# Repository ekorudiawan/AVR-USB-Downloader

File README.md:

# AVR-USB-Downloader
AVR USB Downloader

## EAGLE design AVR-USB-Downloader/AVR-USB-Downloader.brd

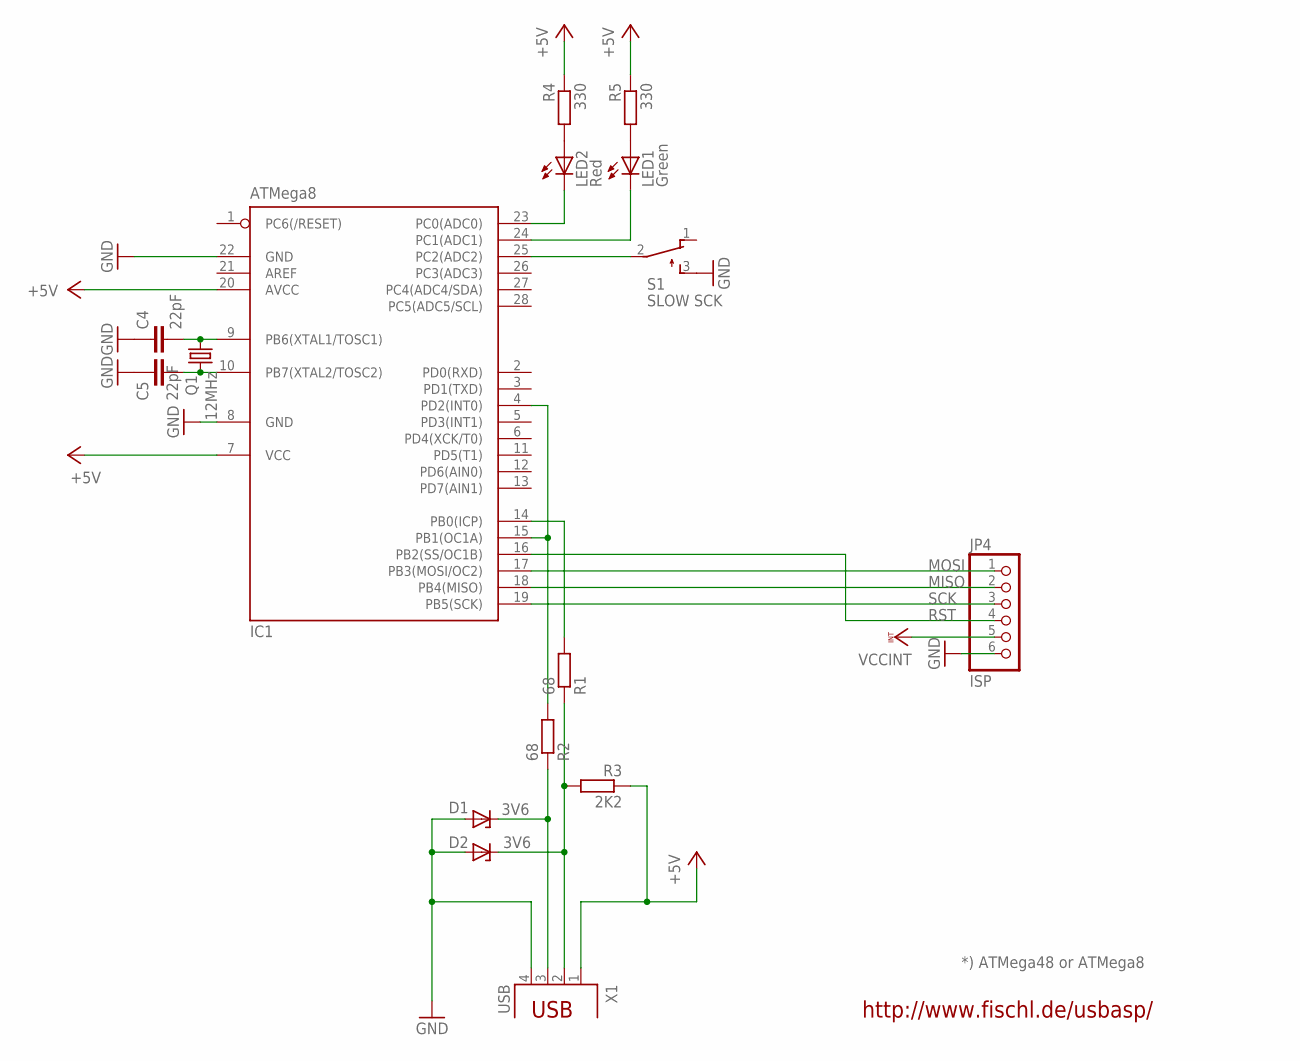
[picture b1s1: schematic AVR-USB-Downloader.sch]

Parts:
C4, C5: 22pF; C025-024X044
D1, D2: 3V6; DO34Z7
IC1: ATMega8; DIL28-3
JP4: ISP; 1X06
LED1: Green; LED3MM
LED2: Red; LED3MM
Q1: 12MHz; HC49/S
R1, R2: 68; 0207/10
R3: 2K2; 0207/10
R4, R5: 330; 0207/10
S1: SLOW SCK; TL3XPO
X1: USB; PN61729

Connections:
+5V: IC1.7 (VCC), IC1.20 (AVCC), R3.1, R4.1, R5.1, X1.1
GND: C4.1, C5.1, D1.A, D2.A, IC1.8 (GND), IC1.22 (GND), JP4.6, S1.3 (S), X1.4
MISO: IC1.18 (PB4(MISO)), JP4.2
MOSI: IC1.17 (PB3(MOSI/OC2)), JP4.1
unnamed: D2.C, R1.1, R3.2, X1.2
unnamed: IC1.4 (PD2(INT0)), IC1.15 (PB1(OC1A)), R2.2
unnamed: D1.C, R2.1, X1.3
unnamed: IC1.25 (PC2(ADC2)), S1.2
unnamed: LED2.A, R4.2
unnamed: IC1.23 (PC0(ADC0)), LED2.K (C)
unnamed: IC1.24 (PC1(ADC1)), LED1.K (C)
unnamed: IC1.14 (PB0(ICP)), R1.2
unnamed: C4.2, IC1.9 (PB6(XTAL1/TOSC1)), Q1.2
unnamed: C5.2, IC1.10 (PB7(XTAL2/TOSC2)), Q1.1
unnamed: LED1.A, R5.2
RST: IC1.16 (PB2(SS/OC1B)), JP4.4
SCK: IC1.19 (PB5(SCK)), JP4.3
VCCINT: JP4.5

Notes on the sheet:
http://www.fischl.de/usbasp/
*) ATMega48 or ATMega8

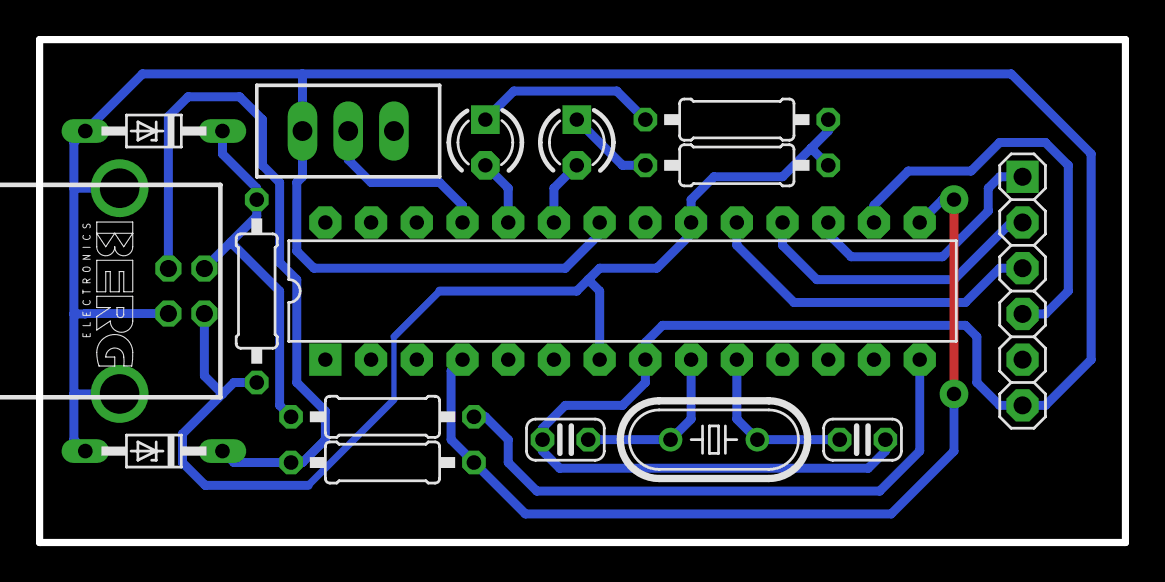
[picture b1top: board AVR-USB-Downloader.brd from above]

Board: 2 copper layers, 60.3 x 27.9 mm, 16 parts (0 on the bottom side), 17 nets.

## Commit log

2017-10-03 Added Files
